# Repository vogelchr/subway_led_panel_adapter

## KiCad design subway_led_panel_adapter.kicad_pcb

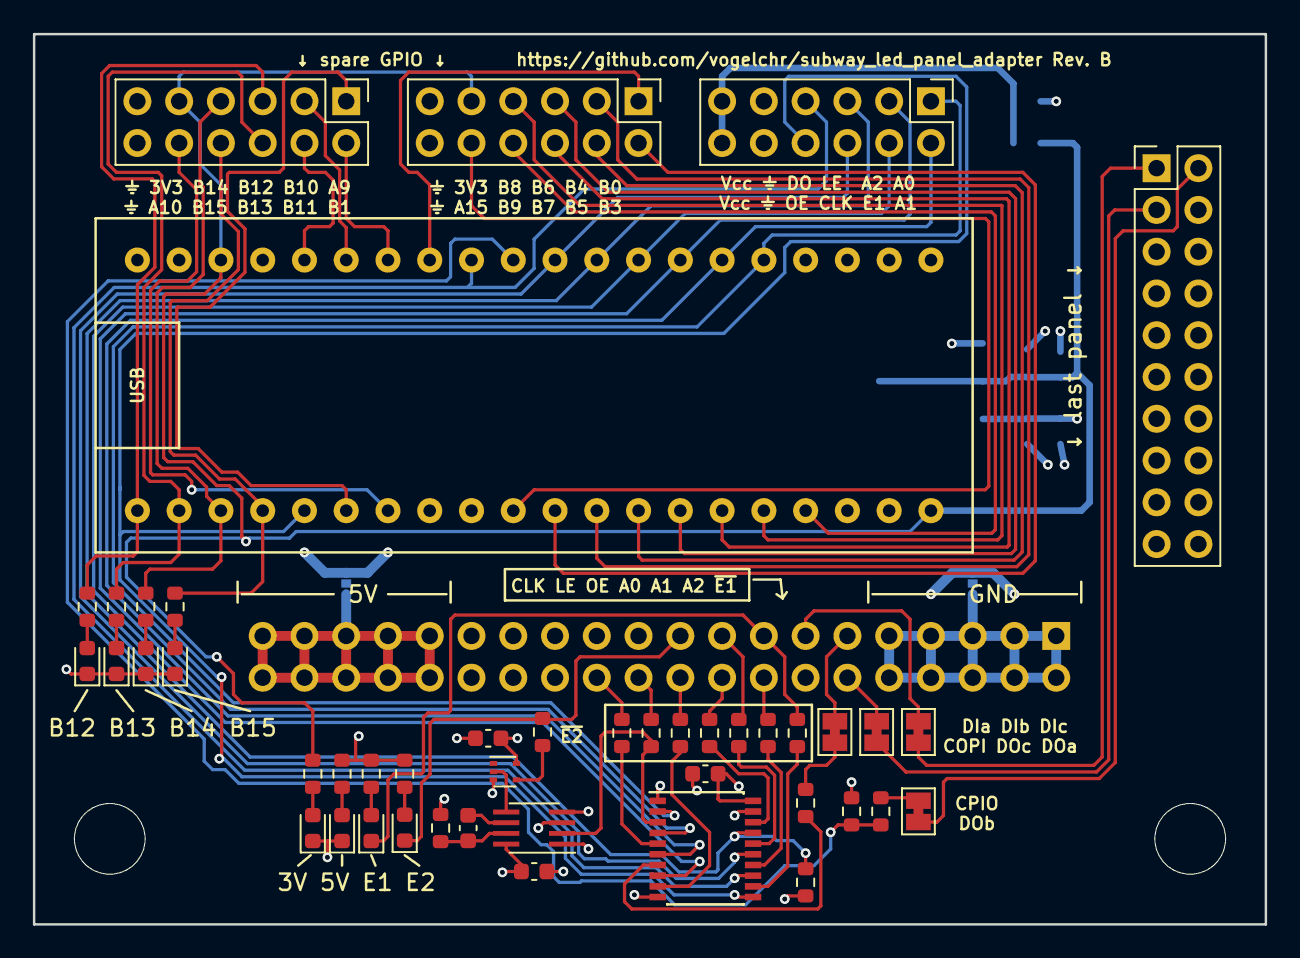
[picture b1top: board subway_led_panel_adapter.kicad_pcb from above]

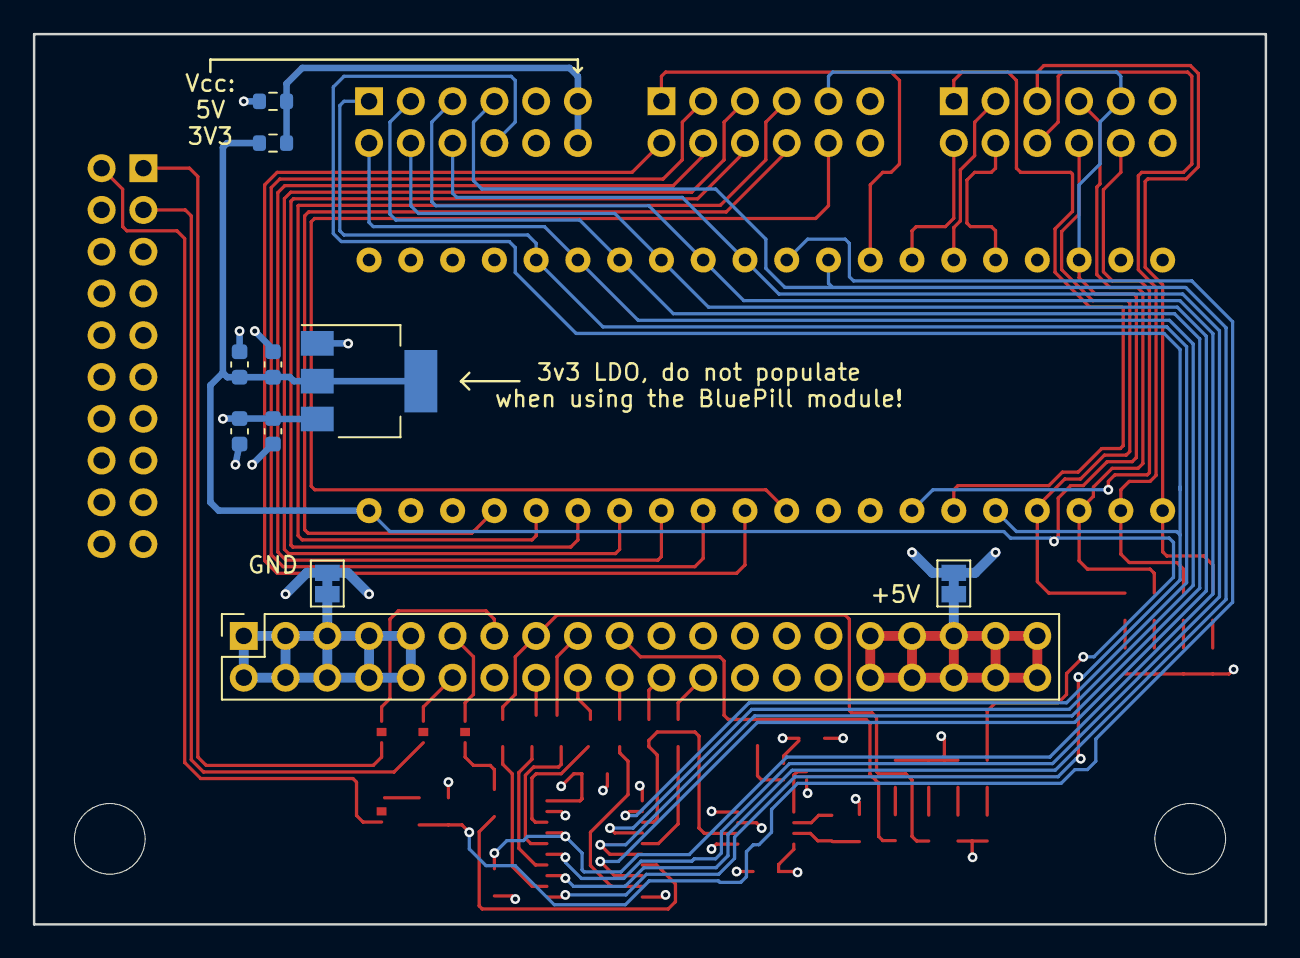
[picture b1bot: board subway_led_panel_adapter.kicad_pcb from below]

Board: 4 copper layers, 74.9 x 54.1 mm, 57 parts (10 on the bottom side), 69 nets.

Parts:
C1, C2, C3, C4, C5, C7: 100n; C_0603_1608Metric
C6, C8: 10u; C_0603_1608Metric
D1, D2, D3, D4, D5, D6, D7, D8: LED; LED_0603_1608Metric
H3, H4: MountingHole; MountingHole_4.3mm_M4
J1, J3, J5: Conn_02x06_Odd_Even; PinHeader_2x06_P2.54mm_Vertical
J2: Conn_02x10_Odd_Even; PinHeader_2x10_P2.54mm_Vertical
J4: Conn_02x20_Odd_Even; PinSocket_2x20_P2.54mm_Vertical
JP1, JP2, JP3, JP4, JP5, JP6: SolderJumper_2_Bridged; SolderJumper-2_P1.3mm_Bridged_Pad1.0x1.5mm
R1: 680R; R_0603_1608Metric
R2, R5, R6, R7, R8, R9, R18, R19, R20, R21: 1k; R_0603_1608Metric
R3: 100k; R_0603_1608Metric
R10, R11, R12, R13, R14, R15, R16, R17, R22: 68R; R_0603_1608Metric
R23: DNP; R_0603_1608Metric
R24: 0R; R_0603_1608Metric
U1: 74AHCT244; SSOP-20_4.4x6.5mm_P0.65mm
U2: ChinaBluePill
U3: 74LVC1G123; SSOP-8_2.95x2.8mm_P0.65mm
U4: 74LVC1GU04DRL; SOT-553
U5: AMS1117-3.3; SOT-223-3_TabPin2

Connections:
+3V3: C7.2, C8.2, J1.9, J3.9, R6.2, R24.2, U2.3V3, U5.2 (VO)
+5V: C1.2, C3.2, C4.2, C5.2, C6.2, JP6.2 (B), R3.2, R5.2, R7.2, R8.2, R23.2, U1.20 (VCC), U3.3 (CLR), U3.8 (VCC), U4.5 (VCC), U5.3 (VI)
/CIPO_5V: JP4.2 (B), R1.1
/CIPO_LV: R1.2, R2.2, U2.PA6
/CLK: J4.24, R15.1
/CLK_LV: J5.6, U1.15 (2A1), U2.PA5
/COPI_5V: JP1.1 (A), R16.1
/COPI_LV: J5.7, U1.13 (2A2), U2.PA7
/DIa: J4.11, JP1.2 (B)
/DIb: J4.12, JP3.2 (B)
/DIc: J4.13, JP2.2 (B)
/DOa: J2.1, JP2.1 (A)
/DOb: J2.2, JP4.1 (A)
/DOc: J2.3, JP3.1 (A)
/LEx: R14.2, U1.3 (2Y0), U3.2 (B)
/LE/MOD/CA: J4.22, R14.1
/LE/MOD/CA_LV: J5.5, R9.2, U1.17 (2A0), U2.PA4
/PA9: J3.1, U2.PA9
/PA10: J3.10, U2.PA10
/PA15: J1.10, U2.PA15
/PB0: J1.1, U2.PB0
/PB1: J3.2, U2.PB1
/PB3: J1.2, U2.PB3
/PB4: J1.3, U2.PB4
/PB5: J1.4, U2.PB5
/PB6: J1.5, U2.PB6
/PB7: J1.6, U2.PB7
/PB8: J1.7, U2.PB8
/PB9: J1.8, U2.PB9
/PB10: J3.3, U2.PB10
/PB11: J3.4, U2.PB11
/PB12: J3.5, R21.2, U2.PB12
/PB13: J3.6, R20.2, U2.PB13
/PB14: J3.7, R19.2, U2.PB14
/PB15: J3.8, R18.2, U2.PB15
/ROW_A0: J4.18, R10.1
/ROW_A0_LV: J5.1, U1.2 (1A0), U2.PA0
/ROW_A1: J4.17, R11.1
/ROW_A1_LV: J5.2, U1.4 (1A1), U2.PA1
/ROW_A2: J4.16, R12.1
/ROW_A2_LV: J5.3, U1.6 (1A2), U2.PA2
/ROW_~E1: D3.1 (K), J4.15, R13.1
/ROW_~E1_LV: J5.4, U1.8 (1A3), U2.PA3
/ROW_~E2: D4.1 (K), J4.19, R22.1
/~OE/SW/~ED_inv: J4.20, R17.1
/~OE/SW/~ED_inv_LV: J5.8, U1.11 (2A3), U2.PA8
GND: C1.1, C3.1, C4.1, C5.1, C6.1, C7.1, C8.1, D1.1 (K), D2.1 (K), D5.1 (K), D6.1 (K), D7.1 (K), D8.1 (K), J1.11, J1.12, J2.11, J2.13, J3.11, J3.12, J4.21, J4.23, J5.9, J5.10, JP5.2 (B), R2.1, R9.1, U1.1 (1OE), U1.10 (GND), U1.19 (2OE), U2.GND, U3.1 (~A), U3.4 (GND), U4.3 (GND), U5.1 (GND)
unnamed: D1.2 (A), R5.1
unnamed: D2.2 (A), R6.1
unnamed: D3.2 (A), R7.1
unnamed: D4.2 (A), R8.1
unnamed: D5.2 (A), R18.1
unnamed: D6.2 (A), R19.1
unnamed: D7.2 (A), R20.1
unnamed: D8.2 (A), R21.1
unnamed: J4.1, J4.2, J4.3, J4.4, J4.5, J4.6, J4.7, J4.8, J4.9, J4.10, JP5.1 (A)
unnamed: J4.31, J4.32, J4.33, J4.34, J4.35, J4.36, J4.37, J4.38, J4.39, J4.40, JP6.1 (A)
unnamed: J5.11, J5.12, R23.1, R24.1
unnamed: R22.2, U4.4
unnamed: R10.2, U1.18 (1Y0)
unnamed: R11.2, U1.16 (1Y1)
unnamed: R12.2, U1.14 (1Y2)
unnamed: R13.2, U1.12 (1Y3)
unnamed: R15.2, U1.5 (2Y1)
unnamed: R16.2, U1.7 (2Y2)
unnamed: R17.2, U1.9 (2Y3)
unnamed: C2.1, U3.6 (Cext)
unnamed: U3.5 (Q), U4.2
unnamed: C2.2, R3.1, U3.7 (RCext)

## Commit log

2021-10-07 Initially empty repository.
2021-10-07 first checkin
2021-10-07 Schematic print on 2021-10-07
2021-10-07 Board print on 2021-10-07.
2021-10-08 more work
2021-10-09 general cleanup
2021-10-10 Add "pmpd" style connector for 3v3 signals, rearrange, add mounting holes.
2021-10-10 Todays schematic print.
2021-10-15 further work
2021-10-15 Rev1 going into fabrication.
2022-06-25 Start working on Rev. B: Adds 3v3 Regulator
2022-07-02 Cleanup rev. B.
